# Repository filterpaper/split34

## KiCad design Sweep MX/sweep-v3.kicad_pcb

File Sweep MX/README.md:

# Sweep MX

Minimalist version of [Sweep High](https://github.com/davidphilipbarr/Sweep/tree/main/Sweep%20High) with:
* Bottom traces with no vias
* No reset buttons
* TRS compatible

Uses `cradio` firmware in QMK and ZMK.

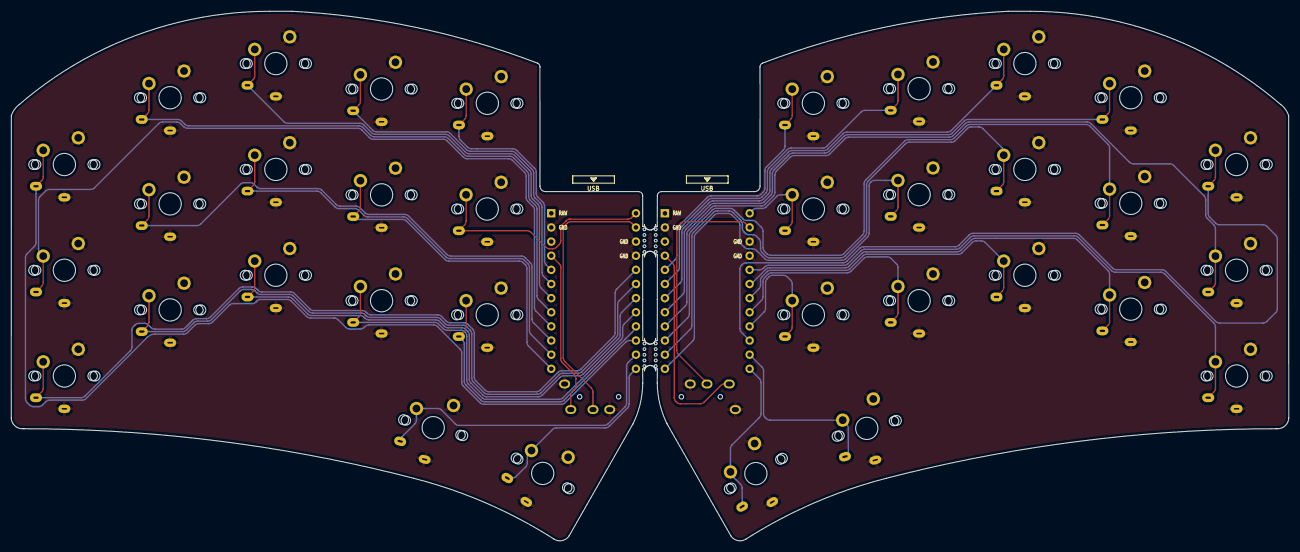
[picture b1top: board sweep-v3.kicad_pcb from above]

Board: 2 copper layers, 229.5 x 95.2 mm, 40 parts (0 on the bottom side), 39 nets.

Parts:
J1, J2: AudioJack4dpb; TRRS-PJ-DPB2
SW2, SW2_r1, SW3, SW3_r1, SW4, SW4_r1, SW5, SW5_r1, SW6, SW6_r1, SW7_r1, SW8, SW8_r1, SW9, SW9_r1, SW10, SW11, SW11_r1, SW12, SW12_r1, SW13_r1, SW14, SW15, SW15_r1, SW16, SW16_r1, SW17, SW17_r1, SW18, SW18_r1, SW20, SW20_r1, SW21, SW21_r1: SW_Push; keyswitch_cherrymx_alps_choc12_1u
U1, U2: ProMicro-kbd; ProMicro_v3_min
mouse-bite-5mm-slot, mouse-bite-5mm-slot#2: VAL**; mouse-bite-5mm-slot-with-space-for-track

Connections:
Switch1: SW2.1, U1.10
Switch1_r: SW2_r1.1, U2.10
Switch2: SW3.1, U1.17
Switch2_r: SW3_r1.1, U2.17
Switch3: SW4.1, U1.18
Switch3_r: SW4_r1.1, U2.18
Switch4: SW5.1, U1.19
Switch4_r: SW5_r1.1, U2.19
Switch5: SW6.1, U1.20
Switch5_r: SW6_r1.1, U2.20
Switch6: SW8.1, U1.16
Switch6_r: SW7_r1.1, U2.16
Switch7: SW9.1, U1.15
Switch7_r: SW8_r1.1, U2.15
Switch8: SW10.1, U1.14
Switch8_r: SW9_r1.1, U2.14
Switch9: SW11.1, U1.13
Switch9_r: SW11_r1.1, U2.13
Switch10: SW12.1, U1.1
Switch10_r: SW12_r1.1, U2.1
Switch11: SW14.1, U1.5
Switch11_r: SW13_r1.1, U2.5
Switch12: SW15.1, U1.6
Switch12_r: SW18_r1.1, U2.6
Switch13: SW16.1, U1.7
Switch13_r: SW15_r1.1, U2.7
Switch14: SW17.1, U1.8
Switch14_r: SW16_r1.1, U2.8
Switch15: SW18.1, U1.9
Switch15_r: SW17_r1.1, U2.9
Switch16: SW21.1, U1.11
Switch16_r: SW21_r1.1, U2.11
Switch17: SW20.1, U1.12
Switch17_r: SW20_r1.1, U2.12
Switch18: J2.R1, U1.2
Switch18_r: J1.R1, U2.2
gnd: J1.R2, J1.S, J2.R2, J2.S, SW2.2, SW2_r1.2, SW3.2, SW3_r1.2, SW4.2, SW4_r1.2, SW5.2, SW5_r1.2, SW6.2, SW6_r1.2, SW7_r1.2, SW8.2, SW8_r1.2, SW9.2, SW9_r1.2, SW10.2, SW11.2, SW11_r1.2, SW12.2, SW12_r1.2, SW13_r1.2, SW14.2, SW15.2, SW15_r1.2, SW16.2, SW16_r1.2, SW17.2, SW17_r1.2, SW18.2, SW18_r1.2, SW20.2, SW20_r1.2, SW21.2, SW21_r1.2, U1.3, U1.4, U1.23, U2.3, U2.4, U2.23
raw: U1.24, U2.24
vcc: J1.T, J2.T, U1.21, U2.21

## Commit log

2022-11-12 Commit Splinter and Sweep
2023-04-06 Add Ika PCB
2023-04-06 Add modified Architeuthis dux
2023-04-06 Update silkscreen and gerbers
2023-04-07 Update Ika traces and gerbers
2023-04-07 Update images
2023-04-12 Fillet traces and silkscreen clean up
2023-04-14 Increase trace curvature
2023-04-20 Add v4 with halftone silks
2023-04-28 Add nice!nano Splinter
